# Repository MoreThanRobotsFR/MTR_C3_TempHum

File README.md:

# MTR_C3_TempHum
A tiny temperature, humidity, gas, pressure, ambient light and presence detector (mmWave presence sensor) measurement unit for HomeAssistant using ESPHome
 
# In progress...

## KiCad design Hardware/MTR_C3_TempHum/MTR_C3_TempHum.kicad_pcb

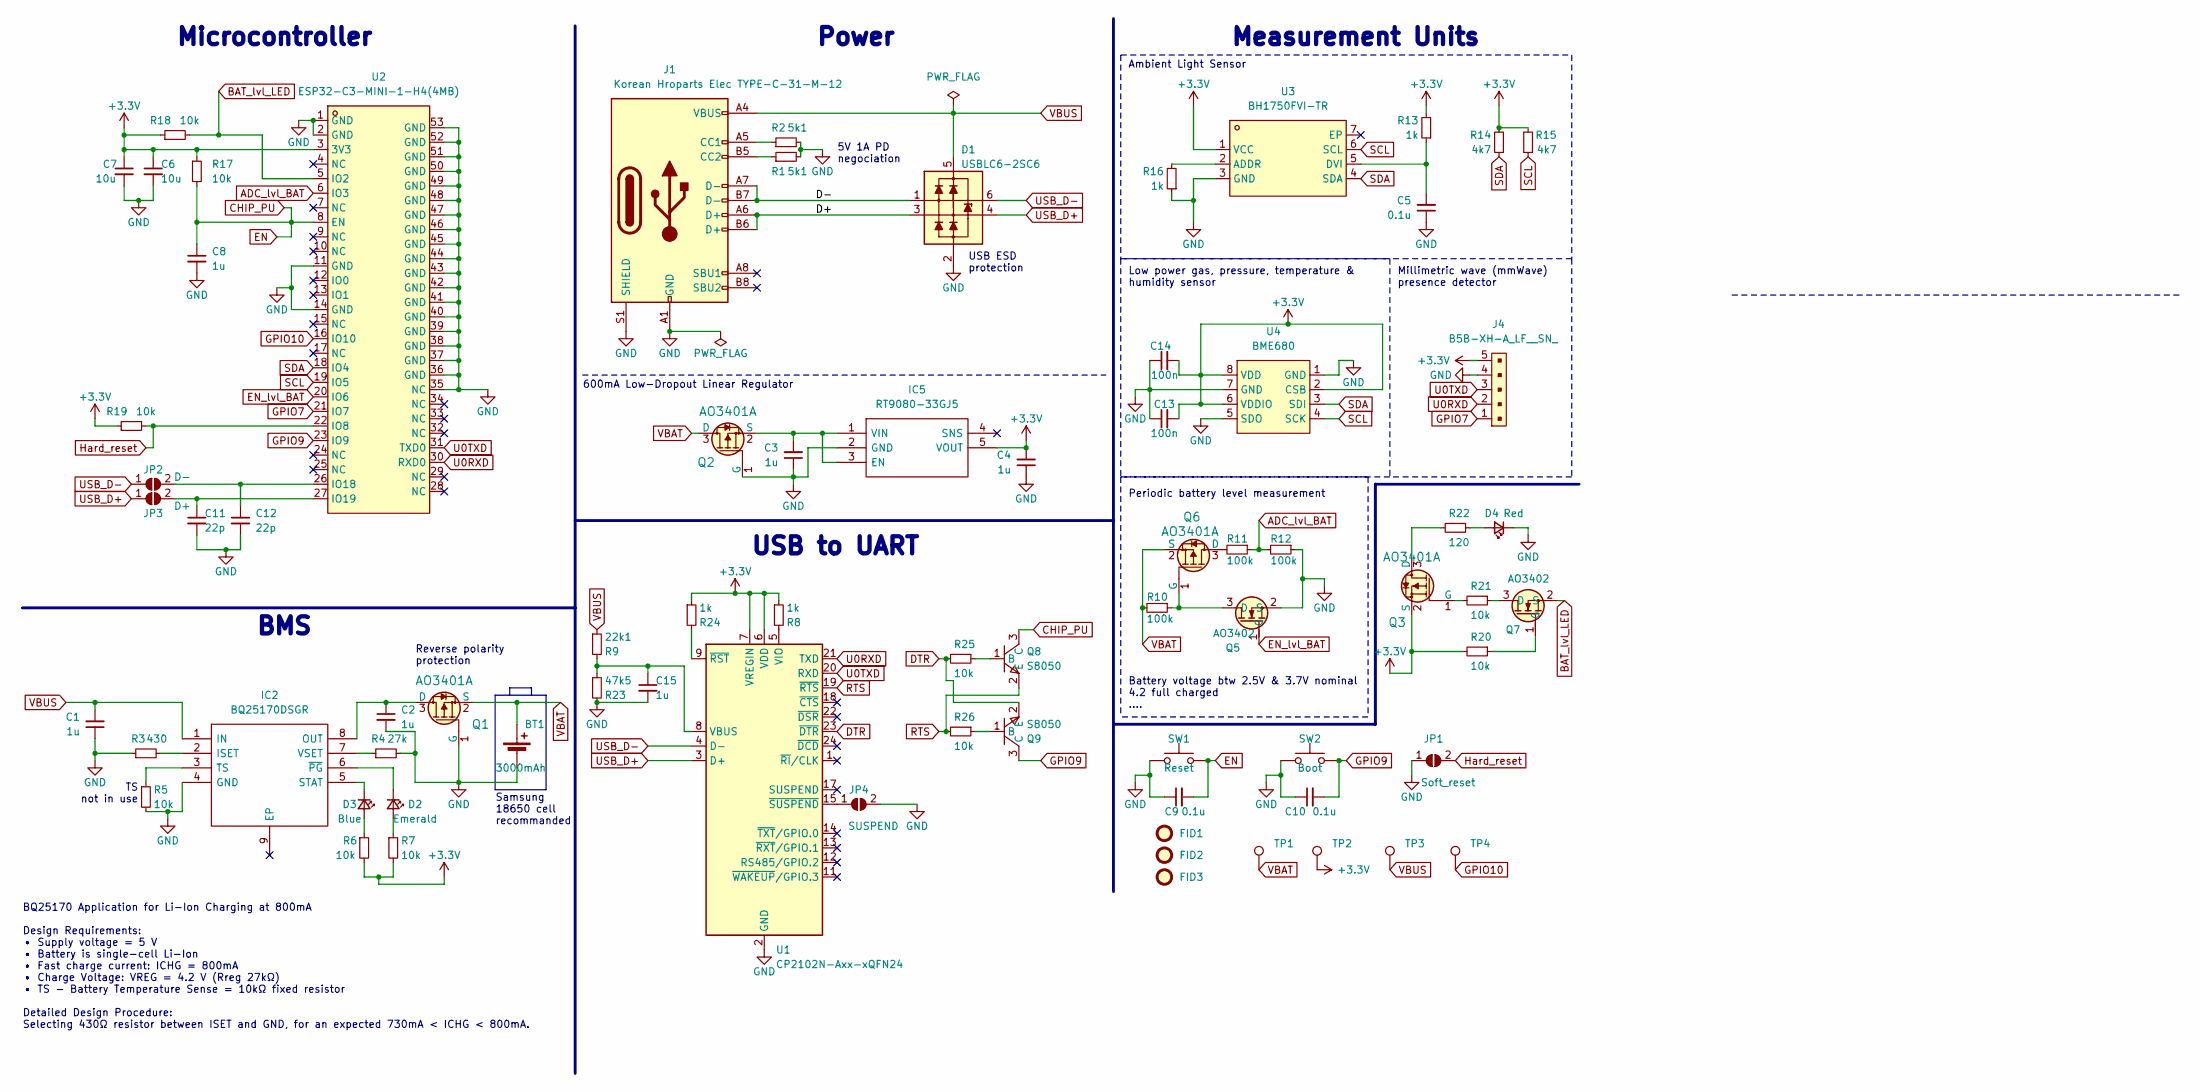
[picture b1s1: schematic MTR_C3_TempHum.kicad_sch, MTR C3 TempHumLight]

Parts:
BT1: 3000mAh; BATTERY-SMD_18650-1S-L77.1-W20.7-1; LCSC C2988620
C1, C2, C3, C4, C8, C15: 1u; R_0402_1005Metric; LCSC C14445
C5, C9, C10: 0.1u; R_0402_1005Metric; LCSC C60474
C6, C7: 10u; R_0402_1005Metric; LCSC C15525
C11, C12: 22p; R_0402_1005Metric; LCSC C14445
C13, C14: 100n; R_0402_1005Metric
D1: USBLC6-2SC6; SOT-23-6_L2.9-W1.6-P0.95-LS2.8-BL; LCSC C7519
D2: Emerald; LED_0603_1608Metric; LCSC C497927
D3: Blue; LED_0603_1608Metric; LCSC C5151484
D4: Red; LED_0603_1608Metric; LCSC C7371906
FID1, FID2, FID3: Fiducial; Fiducial_0.75mm_Mask2.25mm
IC2: BQ25170DSGR; WSON-8_L2.0-W2.0-P0.50-TL-EP; Manufacturer_Part_Number BQ25170DSGR; Mouser Part Number 595-BQ25170DSGR
IC5: RT9080-33GJ5; TSOT-23-5_L2.9-W1.6-P0.95-LS2.8-BL; Manufacturer_Part_Number RT9080-33GJ5; Mouser Part Number 835-RT9080-33GJ5
J1: Korean Hroparts Elec TYPE-C-31-M-12; USB_C_Receptacle_HRO_TYPE-C-31-M-12; LCSC C165948
J4: B5B-XH-A_LF__SN_; PinSocket_1x05_P1.27mm_Vertical; MPN B5B-XH-A(LF)(SN); Digi-Key_PN 455-2270-ND
JP1: Soft_reset; SolderJumper-2_P1.3mm_Open_RoundedPad1.0x1.5mm
JP2: D-; SolderJumper-2_P1.3mm_Open_TrianglePad1.0x1.5mm
JP3: D+; jumper perso1
JP4: SUSPEND; SolderJumper-2_P1.3mm_Open_TrianglePad1.0x1.5mm
Q1, Q2, Q3, Q6: AO3401A; SOT-23; MPN AO3401A; Digi-Key_PN 785-1001-1-ND
Q5, Q7: AO3402; SOT-23; LCSC C14385
Q8, Q9: S8050; SOT-23-3_L2.9-W1.3-P1.90-LS2.4-BR; LCSC Part C909746
R1, R2: 5k1; R_0402_1005Metric; LCSC C25905
R3: 430; R_0402_1005Metric; LCSC C163462
R4: 27k; R_0402_1005Metric; LCSC C138022
R5, R6, R7, R17, R18, R19, R20, R21, R25, R26: 10k; R_0402_1005Metric; LCSC C25744
R8, R13, R16, R24: 1k; R_0402_1005Metric; LCSC C11702
R9: 22k1; R_0402_1005Metric
R10, R11, R12: 100k; R_0402_1005Metric; LCSC C60491
R14, R15: 4k7; R_0402_1005Metric; LCSC C25900
R22: 120; R_0402_1005Metric; LCSC C25079
R23: 47k5; R_0402_1005Metric
SW1: Reset; SW-SMD_L4.0-W3.0-LS5.0; LCSC C2888420
SW2: Boot; SW-SMD_L4.0-W3.0-LS5.0; LCSC C2888420
TP1, TP2, TP3, TP4: TestPoint; TestPoint_Pad_D1.0mm
U1: CP2102N-Axx-xQFN24; QFN-24-1EP_4x4mm_P0.5mm_EP2.6x2.6mm; LCSC C969151
U2: ESP32-C3-MINI-1-H4(4MB); WIFIM-SMD_ESP32-C3-MINI-1; LCSC Part C2934569
U3: BH1750FVI-TR; WSOF-6_L2.6-W1.6-P0.50-TL-EP; LCSC Part C78960
U4: BME680; LGA-8_L3.0-W3.0-P0.80-TR; LCSC Part C125972

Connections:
+3.3V: C4.2, C6.1, C7.1, C13.2, C14.2, IC5.5 (VOUT), J4.5, Q3.2 (S), R6.2, R7.2, R8.1, R13.2, R14.2, R15.2, R17.1, R18.1, R19.1, R20.2, R24.1, TP2.1, U1.6 (VDD), U1.7 (VREGIN), U2.3 (3V3), U3.1 (VCC), U4.2 (CSB), U4.6 (VDDIO), U4.8 (VDD)
/D+: D1.3 (L2), J1.A6 (D+), J1.B6 (D+)
/D-: D1.1 (L1), J1.A7 (D-), J1.B7 (D-)
ADC_lvl_BAT: R11.1, R12.2, U2.6 (IO3)
BAT_lvl_LED: Q7.2 (S), R18.2, U2.5 (IO2)
CHIP_PU: C8.1, C9.2, Q8.3 (C), R17.2, SW1.2, U2.8 (EN)
DTR: Q9.2 (E), R25.2, U1.23 (~DTR)
EN_lvl_BAT: Q5.1 (G), U2.20 (IO6)
GND: BT1.2 (-), C1.1, C2.2, C3.1, C4.1, C5.1, C6.2, C7.2, C8.2, C9.1, C10.1, C11.2, C12.2, C13.1, C14.1, C15.2, D1.2 (VN), D4.1 (K), IC2.4 (GND), IC5.2 (GND), J1.A1 (GND), J1.A12 (GND), J1.B1 (GND), J1.B12 (GND), J1.S1 (SHIELD), J4.4, JP1.1 (A), JP4.2 (B), Q1.1 (G), Q2.1 (G), Q5.2 (S), R1.2, R2.2, R3.1, R4.2, R5.2, R12.1, R16.1, R23.2, SW1.1, SW2.1, U1.2 (GND), U1.25 (GND), U2.1 (GND), U2.2 (GND), U2.11 (GND), U2.14 (GND), U2.35 (NC), U2.36 (GND), U2.37 (GND), U2.38 (GND), U2.39 (GND), U2.40 (GND), U2.41 (GND), U2.42 (GND), U2.43 (GND), U2.44 (GND), U2.45 (GND), U2.46 (GND), U2.47 (GND), U2.48 (GND), U2.49 (GND), U2.50 (GND), U2.51 (GND), U2.52 (GND), U2.53 (GND), U3.3 (GND), U4.1 (GND), U4.5 (SDO), U4.7 (GND)
GPIO7: J4.1, U2.21 (IO7)
GPIO9: C10.2, Q9.3 (C), SW2.2, U2.23 (IO9)
GPIO10: TP4.1, U2.16 (IO10)
Hard_reset: JP1.2 (B), R19.2, U2.22 (IO8)
unnamed: D2.2 (A), R7.1
unnamed: D2.1 (K), IC2.6 (~PG)
unnamed: D3.2 (A), R6.1
unnamed: D3.1 (K), IC2.5 (STAT)
unnamed: D4.2 (A), R22.1
unnamed: IC2.2 (ISET), R3.2
unnamed: C2.1, IC2.8 (OUT), Q1.3 (D)
unnamed: IC2.3 (TS), R5.1
unnamed: IC2.7 (VSET), R4.1
unnamed: C3.2, IC5.1 (VIN), IC5.3 (EN), Q2.2 (S)
unnamed: J1.A5 (CC1), R2.1
unnamed: J1.B5 (CC2), R1.1
unnamed: C12.1, JP2.2 (B), U2.26 (IO18)
unnamed: C11.1, JP3.2 (B), U2.27 (IO19)
unnamed: JP4.1 (A), U1.15 (~SUSPEND)
unnamed: Q3.3 (D), R22.2
unnamed: Q3.1 (G), R21.2
unnamed: Q5.3 (D), Q6.1 (G), R10.1
unnamed: Q6.3 (D), R11.2
unnamed: Q7.3 (D), R21.1
unnamed: Q7.1 (G), R20.1
unnamed: Q8.1 (B), R25.1
unnamed: Q9.1 (B), R26.1
unnamed: C15.1, R9.2, R23.1, U1.8 (VBUS)
unnamed: R8.2, U1.5 (VIO)
unnamed: R24.2, U1.9 (~RST)
unnamed: R16.2, U3.2 (ADDR)
unnamed: C5.2, R13.1, U3.5 (DVI)
RTS: Q8.2 (E), R26.2, U1.19 (~RTS)
SCL: R15.1, U2.19 (IO5), U3.6 (SCL), U4.4 (SCK)
SDA: R14.1, U2.18 (IO4), U3.4 (SDA), U4.3 (SDI)
U0RXD: J4.2, U1.21 (TXD), U2.30 (RXD0)
U0TXD: J4.3, U1.20 (RXD), U2.31 (TXD0)
VBAT: BT1.1 (+), Q1.2 (S), Q2.3 (D), Q6.2 (S), R10.2, TP1.1
VBUS: C1.2, D1.5 (VP), IC2.1 (IN), J1.A4 (VBUS), J1.A9 (VBUS), J1.B4 (VBUS), J1.B9 (VBUS), R9.1, TP3.1

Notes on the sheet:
USB ESD protection
TS not in use
Periodic battery level measurement
Reverse polarity protection
BQ25170 Application for Li-Ion Charging at 800mA Design Requirements: • Supply voltage = 5 V • Battery is single-cell Li-Ion • Fast charge current: ICHG = 800mA • Charge Voltage: VREG = 4.2 V (Rreg 27kΩ) • TS - Battery Temperature Sense = 10kΩ fixed resistor Detailed Design Procedure: Selecting 430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
Power
Battery voltage btw 2.5V & 3.7V nominal 4.2 full charged ....
Millimetric wave (mmWave) presence detector
USB to UART
Low power gas, pressure, temperature & humidity sensor
BMS
Ambient Light Sensor
Measurement Units
5V 1A PD negociation
Samsung 18650 cell recommanded
600mA Low-Dropout Linear Regulator
Microcontroller

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
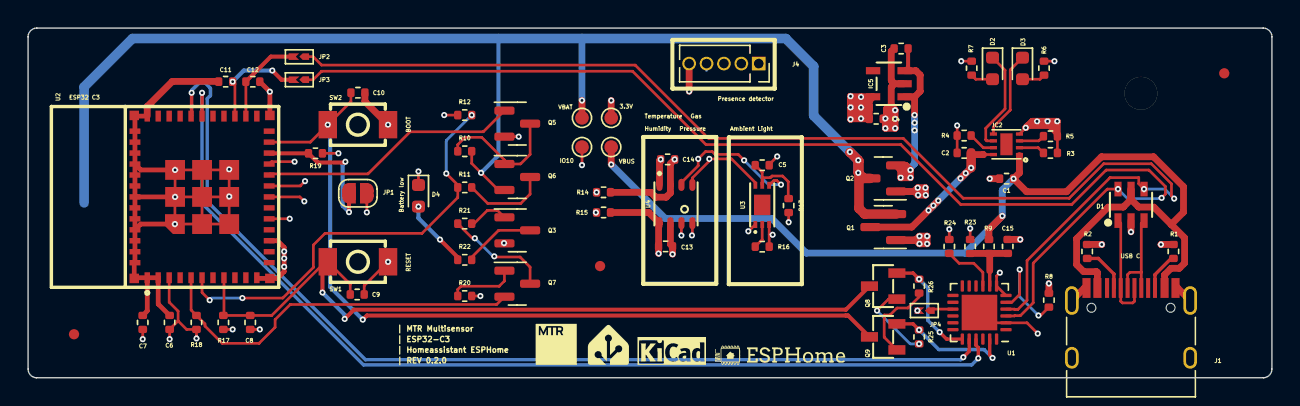
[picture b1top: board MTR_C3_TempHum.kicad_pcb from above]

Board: 4 copper layers, 90.8 x 25.5 mm, 75 parts (1 on the bottom side), 50 nets.

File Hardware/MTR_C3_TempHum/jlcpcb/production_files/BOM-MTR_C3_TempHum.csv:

Comment,Designator,Footprint,LCSC
100n,"C13,C14",R_0402_1005Metric,C110251
1k,"R13,R16,R24,R8",R_0402_1005Metric,C11702
BME680,U4,LGA-8_L3.0-W3.0-P0.80-TR,C125972
27k,R4,R_0402_1005Metric,C138022
AO3402,"Q5,Q7",SOT-23,C14385
1u,"C1,C11,C12,C15,C2,C3,C4,C8",R_0402_1005Metric,C14445
AO3401A,"Q1,Q2,Q3,Q6",SOT-23,C15127
10u,"C6,C7",R_0402_1005Metric,C15525
430,R3,R_0402_1005Metric,C163462
Korean Hroparts Elec TYPE-C-31-M-12,J1,USB_C_Receptacle_HRO_TYPE-C-31-M-12,C165948
120,R22,R_0402_1005Metric,C25079
10k,"R17,R18,R19,R20,R21,R25,R26,R5,R6,R7",R_0402_1005Metric,C25744
47k5,R23,R_0402_1005Metric,C25896
4k7,"R14,R15",R_0402_1005Metric,C25900
5k1,"R1,R2",R_0402_1005Metric,C25905
Reset,"SW1,SW2",SW-SMD_L4.0-W3.0-LS5.0,C2888420
ESP32-C3-MINI-1-H4(4MB),U2,WIFIM-SMD_ESP32-C3-MINI-1,C2934569
3000mAh,BT1,BATTERY-SMD_18650-1S-L77.1-W20.7-1,C2988620
22k1,R9,R_0402_1005Metric,C43473
Emerald,D2,LED_0603_1608Metric,C497927
Blue,D3,LED_0603_1608Metric,C5151484
BQ25170DSGR,IC2,WSON-8_L2.0-W2.0-P0.50-TL-EP,C5208201
0.1u,"C10,C5,C9",R_0402_1005Metric,C60474
100k,"R10,R11,R12",R_0402_1005Metric,C60491
Red,D4,LED_0603_1608Metric,C7371906
USBLC6-2SC6,D1,SOT-23-6_L2.9-W1.6-P0.95-LS2.8-BL,C7519
BH1750FVI-TR,U3,WSOF-6_L2.6-W1.6-P0.50-TL-EP,C78960
RT9080-33GJ5,IC5,TSOT-23-5_L2.9-W1.6-P0.95-LS2.8-BL,C841192
S8050,"Q8,Q9",SOT-23-3_L2.9-W1.3-P1.90-LS2.4-BR,C909746
CP2102N-Axx-xQFN24,U1,QFN-24-1EP_4x4mm_P0.5mm_EP2.6x2.6mm,C969151
B5B-XH-A_LF__SN_,J4,PinSocket_1x05_P1.27mm_Vertical,
SUSPEND,JP4,SolderJumper-2_P1.3mm_Open_TrianglePad1.0x1.5mm,
Soft_reset,JP1,SolderJumper-2_P1.3mm_Open_RoundedPad1.0x1.5mm,
D+,JP3,jumper perso1,
D-,JP2,SolderJumper-2_P1.3mm_Open_TrianglePad1.0x1.5mm,
Fiducial,FID3,Fiducial_0.75mm_Mask2.25mm,
Fiducial,FID2,Fiducial_0.75mm_Mask2.25mm,
Fiducial,FID1,Fiducial_0.75mm_Mask2.25mm,
TestPoint,TP4,TestPoint_Pad_D1.0mm,
TestPoint,TP3,TestPoint_Pad_D1.0mm,
TestPoint,TP2,TestPoint_Pad_D1.0mm,
TestPoint,TP1,TestPoint_Pad_D1.0mm,

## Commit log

2023-11-12 V0.0.1
2024-02-13 REV 0.1
2024-03-24 V0.2.0
2024-04-11 HTML BOM
